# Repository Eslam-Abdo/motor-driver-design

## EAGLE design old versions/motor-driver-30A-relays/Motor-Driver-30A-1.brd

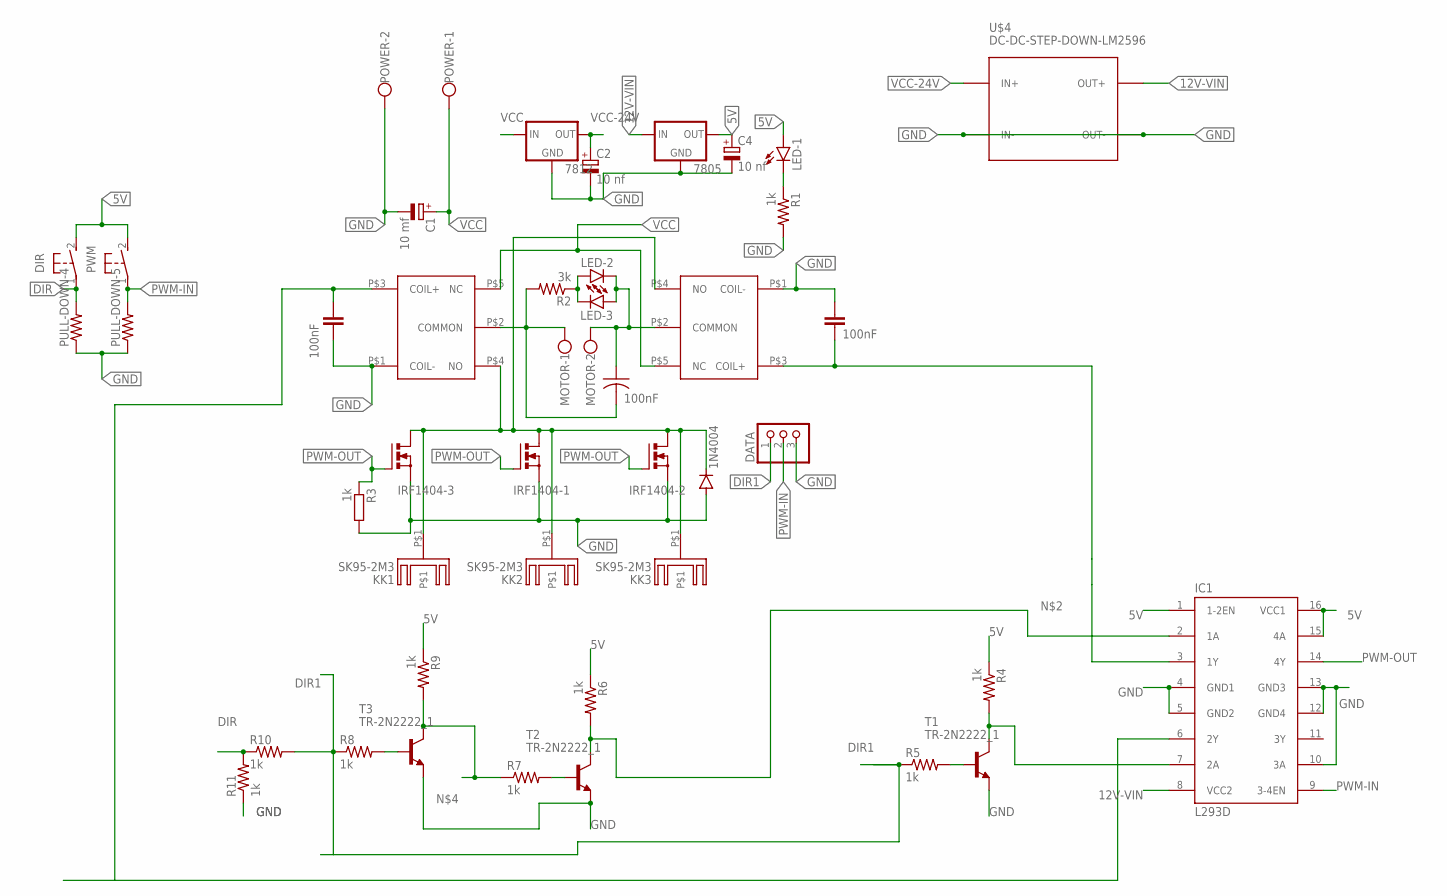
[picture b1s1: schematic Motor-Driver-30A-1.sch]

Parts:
7805, 7812: 78XXL
C1: 10 mf; E2,5-7
C2, C4: 10 nf; E2,5-7
DATA: PINHD-3_DATA; 1X03_DATA
DIR: PUSHBOTTON; B3F-10XX
IC1: L293D; DIL16
IRF1404-1, IRF1404-2, IRF1404-3: PMOSFET_NTO220BV; TO220BV
KK1, KK2, KK3: SK95-2M3
LED-1, LED-2, LED-3: LED3MM
MOTOR: W239-302
POWER: W239-302
PULL-DOWN-4: R-US_0204/7; 0204/7
PULL-DOWN-5: R-US_0204/2V; 0204V
PWM: PUSHBOTTON; B3F-10XX
R1, R7, R10, R11: 1k; 0204V
R2: 3k; 0207/10
R3, R4, R6, R9: 1k; 0204/7
R5, R8: 1k; 0204/5
REVERSE-CURRENT: 1N4004; DO41-10
T1, T2, T3: TR-2N2222_1; TO92-EBC
U$1, U$2: RELAY-30A
U$3, U$5: 100nF; C025-025X050
U$4: DC-DC-STEP-DOWN-LM2596
U$6: 100nF; C075-032X103

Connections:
003: IC1.3 (1Y), U$2.P$3 (COIL+), U$5.2
5V: 7805.OUT, C4.+, DIR.2 (S), IC1.1 (1-2EN), IC1.15 (4A), IC1.16 (VCC1), LED-1.A, PWM.2 (S), R4.1, R6.1, R9.1
12V-VIN: 7805.IN, IC1.8 (VCC2), U$4.OUT+
45464: IC1.6 (2Y), U$1.P$3 (COIL+), U$3.1
DIR: DIR.1, PULL-DOWN-4.2, R10.1, R11.2
DIR1: DATA.1, R5.1, R8.1, R10.2
GND: 7805.GND, 7812.GND, C1.-, C2.-, C4.-, DATA.3, IC1.4 (GND1), IC1.5 (GND2), IC1.10 (3A), IC1.12 (GND4), IC1.13 (GND3), IRF1404-1.S, IRF1404-2.S, IRF1404-3.S, POWER.2, PULL-DOWN-4.1, PULL-DOWN-5.1, R1.2, R3.2, R11.1, REVERSE-CURRENT.A, T1.E, T2.E, T3.E, U$1.P$1 (COIL-), U$2.P$1 (COIL-), U$3.2, U$4.IN-, U$4.OUT-, U$5.1
unnamed: MOTOR.1, R2.2, U$1.P$2 (COMMON), U$6.2
unnamed: IC1.2 (1A), R6.2, T2.C
unnamed: LED-2.A, LED-3.K (C), R2.1
unnamed: R7.1, R9.2, T3.C
unnamed: IRF1404-1.D, IRF1404-2.D, IRF1404-3.D, KK1.P$1, KK2.P$1, KK3.P$1, REVERSE-CURRENT.C, U$1.P$4 (NO), U$2.P$4 (NO)
unnamed: IC1.7 (2A), R4.2, T1.C
unnamed: R5.2, T1.B
unnamed: R7.2, T2.B
unnamed: LED-1.K (C), R1.1
unnamed: R8.2, T3.B
unnamed: LED-2.K (C), LED-3.A, MOTOR.2, U$2.P$2 (COMMON), U$6.1
PWM-IN: DATA.2, IC1.9 (3-4EN), PULL-DOWN-5.2, PWM.1
PWM-OUT: IC1.14 (4Y), IRF1404-1.G, IRF1404-2.G, IRF1404-3.G, R3.1
VCC: 7812.IN, C1.+, POWER.1, U$1.P$5 (NC), U$2.P$5 (NC)
VCC-24V: 7812.OUT, C2.+, U$4.IN+

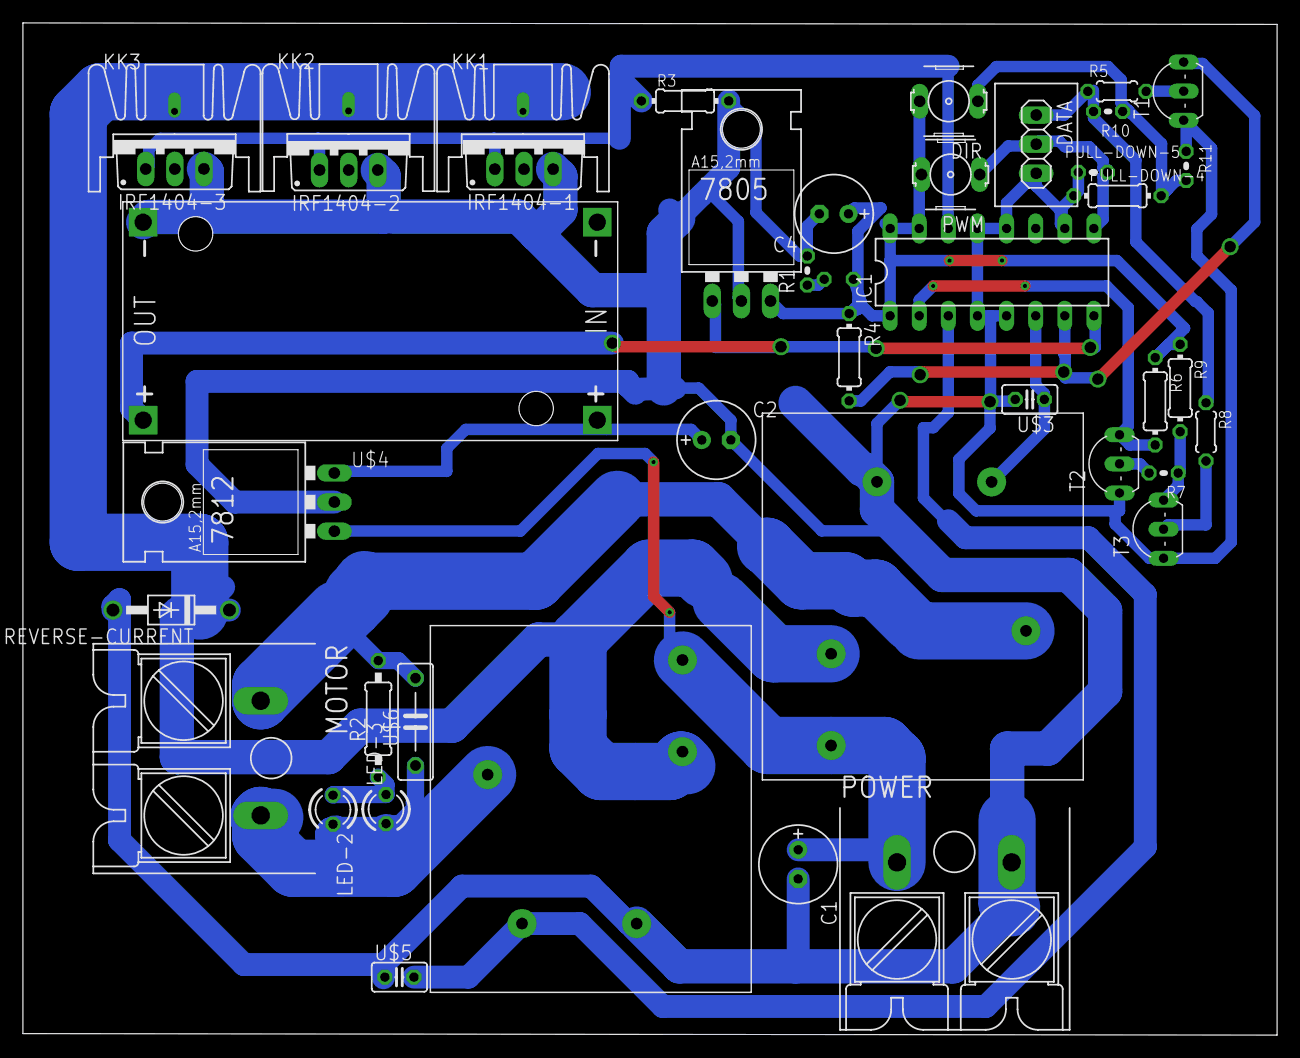
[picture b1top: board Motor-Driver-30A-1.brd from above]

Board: 2 copper layers, 109.4 x 88.3 mm, 43 parts (1 on the bottom side), 22 nets.

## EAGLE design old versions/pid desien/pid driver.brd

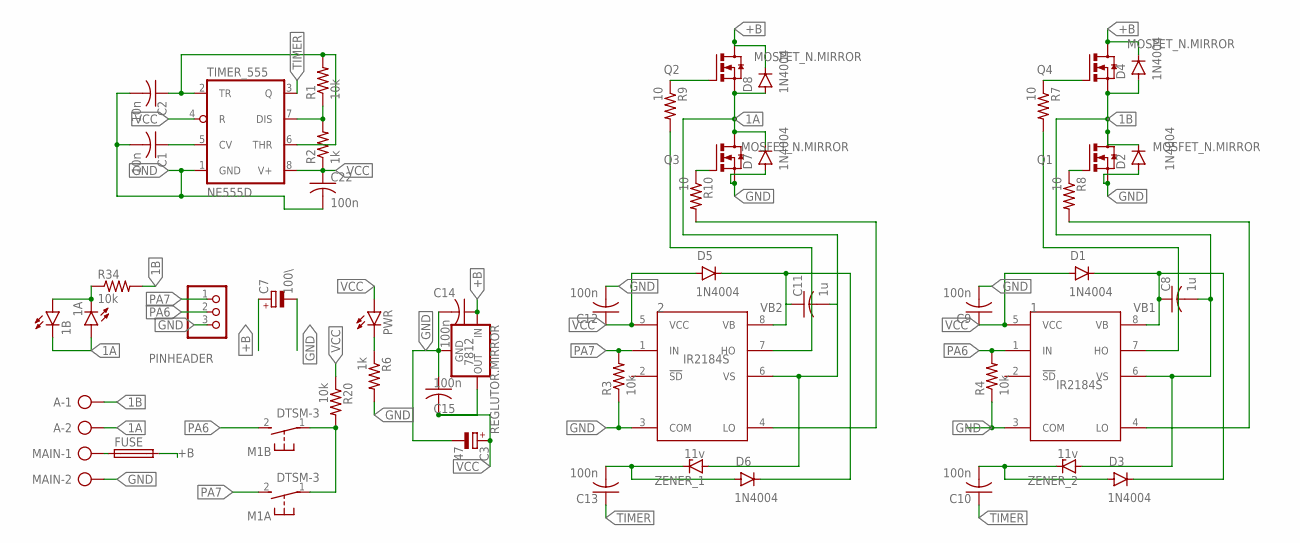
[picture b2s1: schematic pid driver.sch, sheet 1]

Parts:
1, 2: IR2184S; SO08
1A, 1B: LEDCHIPLED_1206; CHIPLED_1206
7812: REGLUTOR.MIRROR; 78XXL.MIRROR
A: AK300/22; XTALRR488W60L1090T465H350B
C1, C2: 10n; C1206K
C3: 47; E5-10,5
C7: 100\; E5-10,5
C8, C11: 1u; C1206K
C9, C10, C12, C13, C14, C15, C22: 100n; C1206K
D1, D2, D3, D4, D5, D6, D7, D8: 1N4004; DO41-10
FUSE: FUSE_HOLDER; SH22,5A
M1A, M1B: DTSM-3
MAIN: AK300/22; XTALRR488W60L1090T465H350B
PINHEADER: PINHD-1X3; 1X03
PWR: LEDCHIPLED_1206; CHIPLED_1206
Q1, Q2, Q3, Q4: MOSFET_N.MIRROR; TO220.MIRROR
R1, R3, R4, R20, R34: 10k; M1206
R2, R6: 1k; M1206
R7, R8, R9, R10: 10; M1206
TIMER_555: NE555D; SO08
ZENER_1, ZENER_2: 11v; SOD81

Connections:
1A: 1A.A, 1B.C, 2.6 (VS), A.2, C11.2, D7.C, D8.A, Q2.S, Q3.D, ZENER_1.A
1B: 1.6 (VS), A.1, C8.2, D2.C, D4.A, Q1.D, Q4.S, R34.2, ZENER_2.A
+B: 7812.IN, C7.+, C14.1, D4.C, D8.C, FUSE.2, Q2.D, Q4.D
GND: 1.3 (COM), 2.3 (COM), 7812.GND, C1.2, C2.2, C3.-, C7.-, C9.2, C12.2, C14.2, C15.1, C22.2, D2.A, D7.A, MAIN.2, PINHEADER.3, Q1.S, Q3.S, R3.1, R4.1, R6.2, TIMER_555.1 (GND); also elsewhere on the board
unnamed: PWR.C, R6.1
unnamed: C1.1, TIMER_555.5 (CV)
unnamed: R1.1, R2.2, TIMER_555.7 (DIS)
unnamed: C2.1, R1.2, TIMER_555.2 (TR), TIMER_555.6 (THR)
unnamed: M1A.1, M1B.1, R20.2
unnamed: Q4.G, R7.1
unnamed: Q1.G, R8.1
unnamed: 1.4 (LO), R8.2
unnamed: 1.7 (HO), R7.2
unnamed: C10.2, D3.A, ZENER_2.C
unnamed: Q3.G, R10.1
unnamed: Q2.G, R9.1
unnamed: 2.4 (LO), R10.2
unnamed: 2.7 (HO), R9.2
unnamed: C13.2, D6.A, ZENER_1.C
unnamed: FUSE.1, MAIN.1
unnamed: 1A.C, 1B.A, R34.1
PA6: 1.1 (IN), M1B.2, PINHEADER.2, R4.2
PA7: 2.1 (IN), M1A.2, PINHEADER.1, R3.2
TIMER: C10.1, C13.1, TIMER_555.3 (Q)
VB1: 1.8 (VB), C8.1, D1.C, D3.C
VB2: 2.8 (VB), C11.1, D5.C, D6.C
VCC: 1.5 (VCC), 2.5 (VCC), 7812.OUT, C3.+, C9.1, C12.1, C15.2, C22.1, D1.A, D5.A, PWR.A, R2.1, R20.1, TIMER_555.4 (R), TIMER_555.8 (V+)

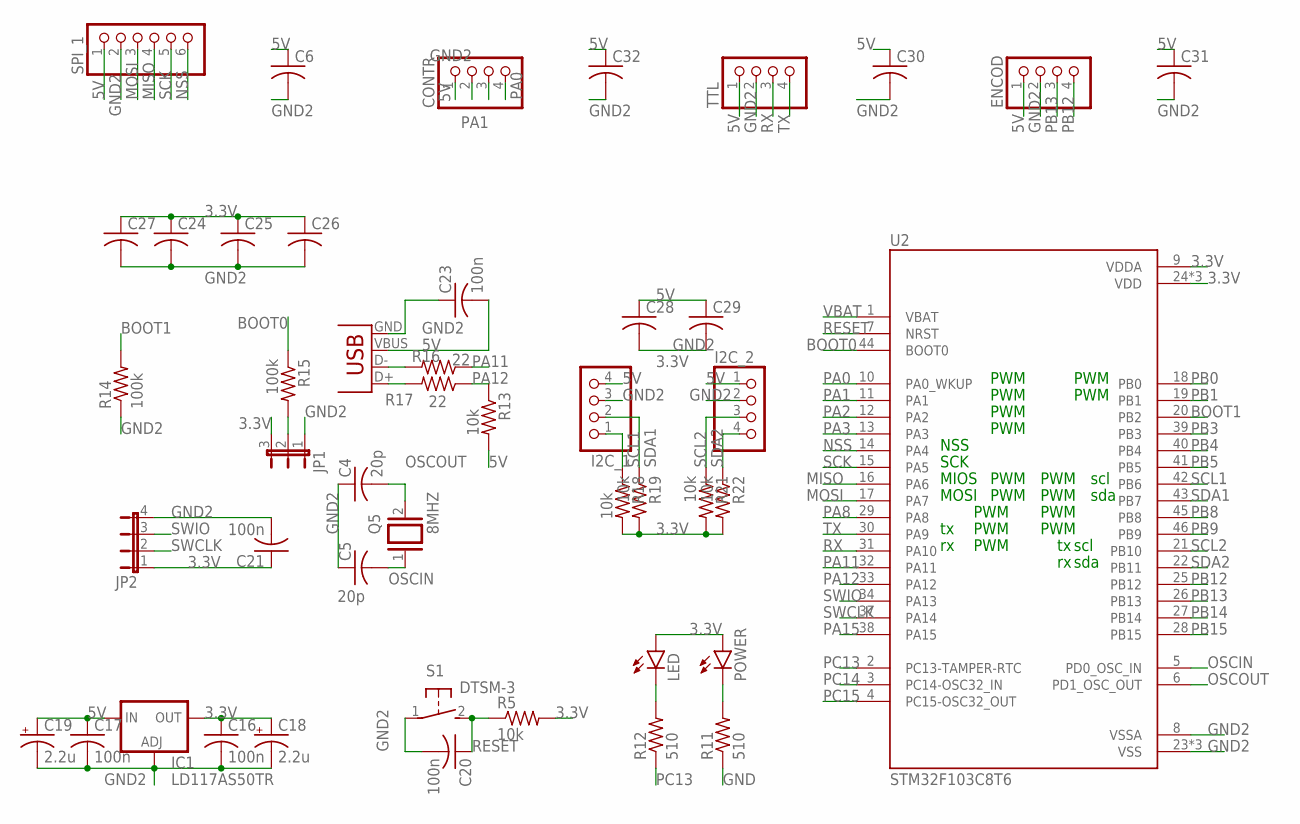
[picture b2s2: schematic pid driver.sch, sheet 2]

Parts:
C4, C5: 20p; C1206
C6, C24, C25, C26, C27, C28, C29, C30, C31, C32: C-USC1206; C1206
C16, C17, C20, C21, C23: 100n; C1206
C18, C19: 2.2u; E2-5
CONTR: PINHD-1X4; 1X04
ENCOD: PINHD-1X4; 1X04
I2C_1, I2C_2: PINHD-1X4; 1X04
IC1: LD117AS50TR; SOT223
JP1: JP2E; JP2
JP2: JP4E; JP4
LED: LEDCHIPLED_1206; CHIPLED_1206
POWER: LEDCHIPLED_1206; CHIPLED_1206
Q5: 8MHZ; QS
R5, R13, R18, R19, R21, R22: 10k; R1206
R11, R12: 510; R1206
R14, R15: 100k; R1206
R16, R17: 22; R1206
S1: DTSM-3
SPI_1: PINHD-1X6; 1X06
TTL: PINHD-1X4; 1X04
U2: STM32F103C8T6; QFP50P900X900X160-48N
X1: USB-MB-S

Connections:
3.3V: C16.1, C18.+, C21.1, C24.1, C25.1, C26.1, C27.1, IC1.4 (OUT), JP1.3, JP2.1, LED.A, POWER.A, R5.2, R18.2, R19.2, R21.2, R22.2, U2.9 (VDDA), U2.24 (VDD), U2.36 (VDD), U2.48 (VDD)
5V: C6.1, C17.1, C19.+, C23.2, C28.1, C29.1, C30.1, C31.1, C32.1, CONTR.1, ENCOD.1, I2C_1.4, I2C_2.1, IC1.3 (IN), R13.2, SPI_1.1, TTL.1, X1.VBUS
BOOT0: R15.1, U2.44 (BOOT0)
BOOT1: R14.2, U2.20 (PB2)
GND: R11.1; also elsewhere on the board
GND2: C4.1, C5.1, C6.2, C16.2, C17.2, C18.-, C19.-, C20.2, C21.2, C23.1, C24.2, C25.2, C26.2, C27.2, C28.2, C29.2, C30.2, C31.2, C32.2, CONTR.2, ENCOD.2, I2C_1.3, I2C_2.2, IC1.1 (ADJ), JP1.1, JP2.4, R14.1, S1.1, SPI_1.2, TTL.2, U2.8 (VSSA), U2.23 (VSS), U2.35 (VSS), U2.47 (VSS), X1.GND
MISO: SPI_1.4, U2.16 (PA6)
MOSI: SPI_1.3, U2.17 (PA7)
unnamed: LED.C, R12.2
unnamed: POWER.C, R11.2
unnamed: JP1.2, R15.2
unnamed: R16.2, X1.D-
unnamed: R17.2, X1.D+
NSS: SPI_1.6, U2.14 (PA4)
OSCIN: C5.2, Q5.1, U2.5 (PD0_OSC_IN)
OSCOUT: C4.2, Q5.2, U2.6 (PD1_OSC_OUT)
PA0: CONTR.4, U2.10 (PA0_WKUP)
PA1: CONTR.3, U2.11 (PA1)
PA2: U2.12 (PA2)
PA3: U2.13 (PA3)
PA8: U2.29 (PA8)
PA11: R16.1, U2.32 (PA11)
PA12: R13.1, R17.1, U2.33 (PA12)
PA15: U2.38 (PA15)
PB0: U2.18 (PB0)
PB1: U2.19 (PB1)
PB3: U2.39 (PB3)
PB4: U2.40 (PB4)
PB5: U2.41 (PB5)
PB8: U2.45 (PB8)
PB9: U2.46 (PB9)
PB12: ENCOD.4, U2.25 (PB12)
PB13: ENCOD.3, U2.26 (PB13)
PB14: U2.27 (PB14)
PB15: U2.28 (PB15)
PC13: R12.1, U2.2 (PC13-TAMPER-RTC)
PC14: U2.3 (PC14-OSC32_IN)
PC15: U2.4 (PC15-OSC32_OUT)
RESET: C20.1, R5.1, S1.2, U2.7 (NRST)
RX: TTL.3, U2.31 (PA10)
SCK: SPI_1.5, U2.15 (PA5)
SCL1: I2C_1.1, R18.1, U2.42 (PB6)
SCL2: I2C_2.3, R21.1, U2.21 (PB10)
SDA1: I2C_1.2, R19.1, U2.43 (PB7)
SDA2: I2C_2.4, R22.1, U2.22 (PB11)
SWCLK: JP2.2, U2.37 (PA14)
SWIO: JP2.3, U2.34 (PA13)
TX: TTL.4, U2.30 (PA9)
VBAT: U2.1 (VBAT)

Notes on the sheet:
scl
sda
MOSI
MIOS
SCK
NSS
PWM

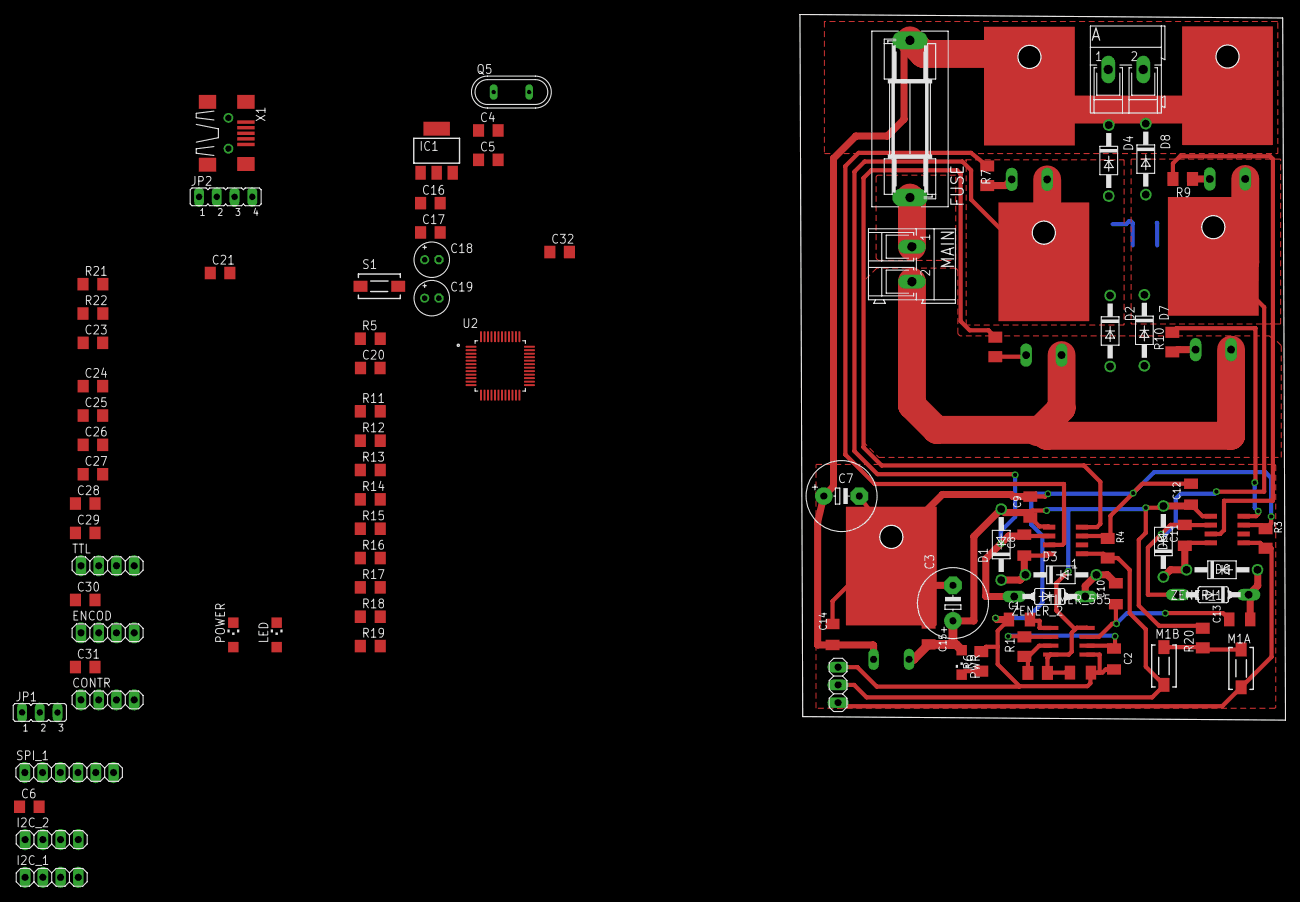
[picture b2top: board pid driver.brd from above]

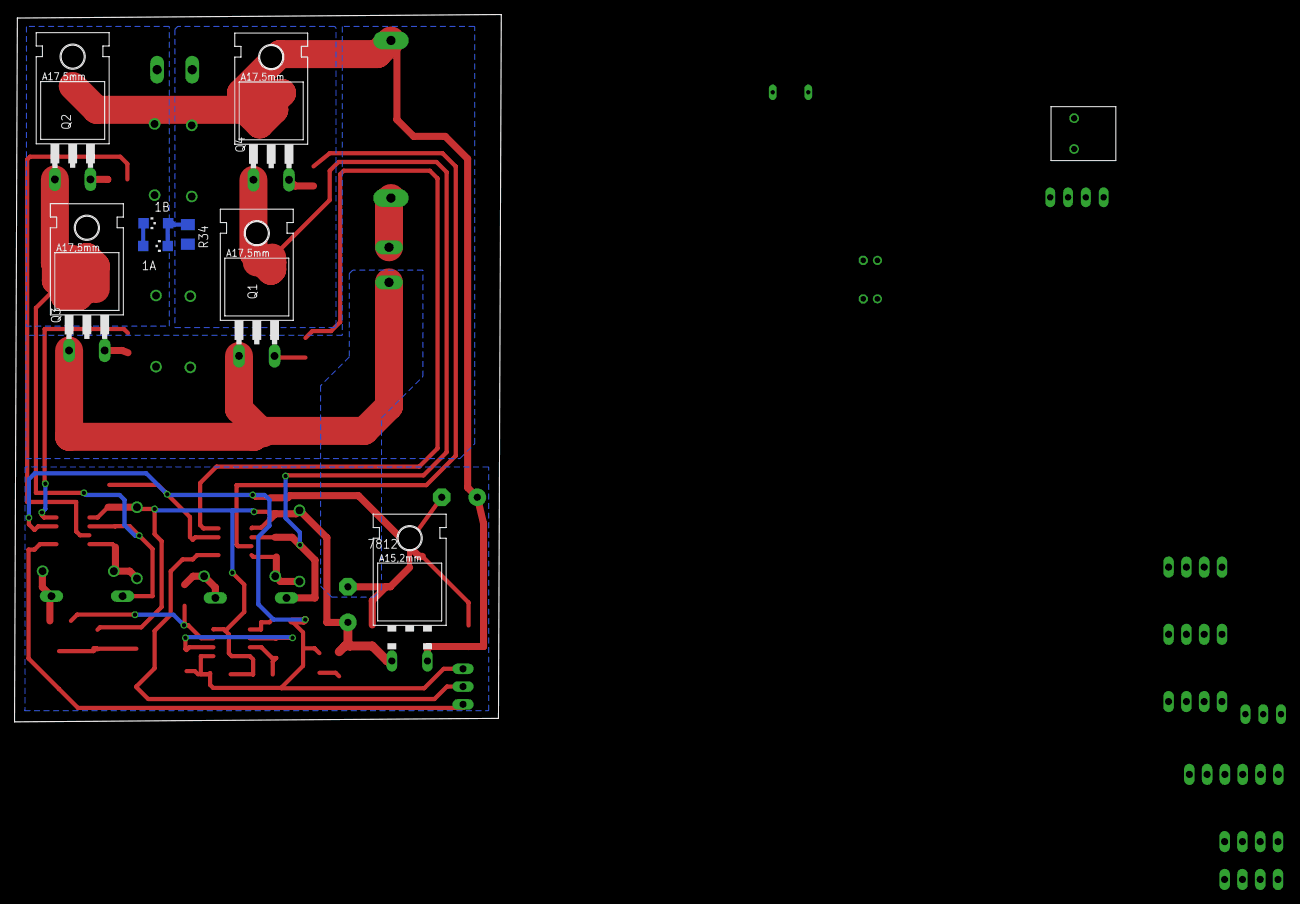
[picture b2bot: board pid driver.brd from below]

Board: 2 copper layers, 69.5 x 101.0 mm, 97 parts (8 on the bottom side), 59 nets.
